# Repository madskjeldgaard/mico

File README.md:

# Mico - A tiny, cheap Raspberry Pi Pico midi controller

Mico is a small, cheap (~10 euros total) and super precise 14 bit midi controller based on the [Raspberry Pi Pico board](https://www.raspberrypi.com/products/raspberry-pi-pico/).

## Features
- 4 x detentless (smooth) encoders 
- Velocity: Slow movements result in microscopic changes (1/16000 of the max range approximately), fast movements in large changes.
- A variety of "clip modes" (cycle through them by pressing the button):
 	- wrap (when the value goes above max, it wraps back to 0) 
 	- clamp (clip at min and max value)
- 14 bit midi (as well as regular 7 bit midi)
- Cheap as chips and open sourced

## DEMO

There's a [demo here](https://vimeo.com/723291413).

## BOM

| Quantity | Part | Mouser Number |
|---|---|---|
| 1 | Raspberry Pi Pico rpi2040 | [474-DEV-17829](https://no.mouser.com/ProductDetail/SparkFun/DEV-17829?qs=sGAEpiMZZMv0NwlthflBi8NxDpSYKEiM3fbb2%2FVBX4k%3D) |
| 8 | 0.01uF capacitor, 0603 | [80-C0603C103M5R7411](https://no.mouser.com/ProductDetail/KEMET/C0603C103M5RAC7411?qs=ACslrEyEXNOtANB4TBkCnQ%3D%3D) |
| 16 | 10k resistors, 1%, 0603 | [603-RC0603FR-0710KL](https://no.mouser.com/ProductDetail/YAGEO/RC0603FR-0710KL?qs=sGAEpiMZZMtlubZbdhIBIAhzU1Tw%252BHVakiDuQ4Zki0U%3D) |
| 4 | 15mm Detentless encoders | [652-PEC11R-4015K-N24](https://no.mouser.com/ProductDetail/652-PEC11R-4015K-N24)(knurled) / [PEC11R-4015F-N0024](https://no.mouser.com/ProductDetail/Bourns/PEC11R-4015F-N0024)(flat) |
| 2 | Female header (to sandwich between the boards)| n/a |
| 2 | Male header (to sandwich between the boards) | n/a |

## Uploading the firmware

Download the latest firmware from the release and locate the `mico.uf2` file. While plugging your Pico into your computer, press and hold the "BOOTSEL" button. It will show up as a storage device on your computer. Copy `mico.uf2` to this device. Done.

## Building and uploading the firmware (optional)

If you want to build the code and mess around with it, it is recommended to use a second Pico flashed with the [picoprobe](https://github.com/raspberrypi/picoprobe) firmware.

### Using picoprobe

```bash
cd software
mkdir build
cd build 
cmake ..
make && openocd -f interface/picoprobe.cfg -f target/rp2040.cfg -c "program mico.elf verify reset exit"
```
Debug:
```bash
openocd -f interface/picoprobe.cfg -f target/rp2040.cfg -s tcl
```

## Usage

### SuperCollider

There is an easy to use interface for this controller [here](https://github.com/madskjeldgaard/mico-sc).

## License

This work is shared under the *Attribution-NonCommercial-ShareAlike 4.0 International* license.

If you have questions about that, send me an email **mail at madskjeldgaard.dk**

## Credits

These projects were a big help and inspiration in making this:
- [schatzmann blog](https://www.pschatzmann.ch/home/2021/02/15/usb-midi-on-the-arduino-pico/) and [also this post](https://www.pschatzmann.ch/home/2021/02/19/tinyusb-a-simple-tutorial/)
- [pico-example-midi](https://github.com/infovore/pico-example-midi)
- [encoder-pio](https://github.com/pimoroni/pimoroni-pico) is from the pimoroni-pico library. MIT Licensed.

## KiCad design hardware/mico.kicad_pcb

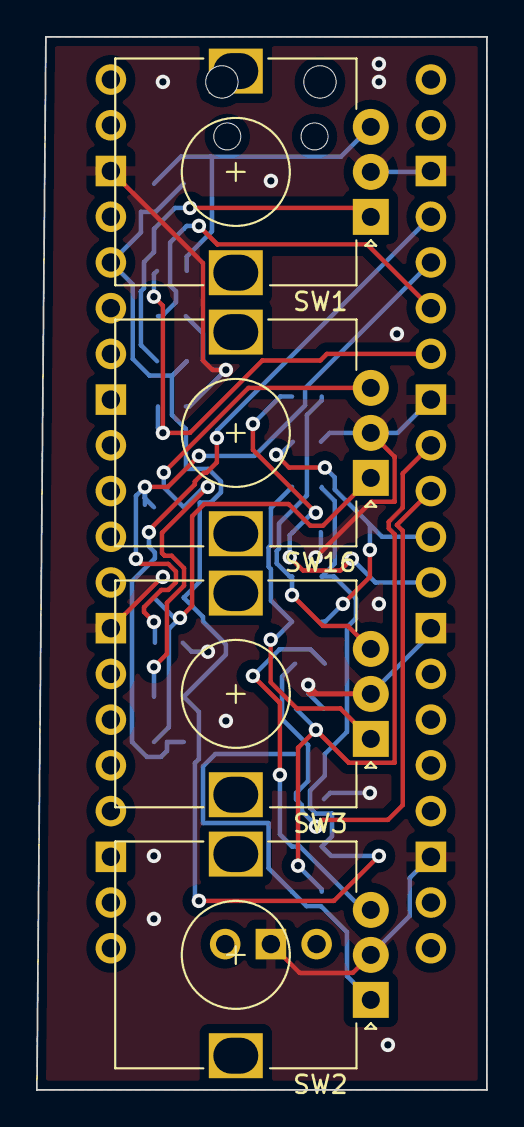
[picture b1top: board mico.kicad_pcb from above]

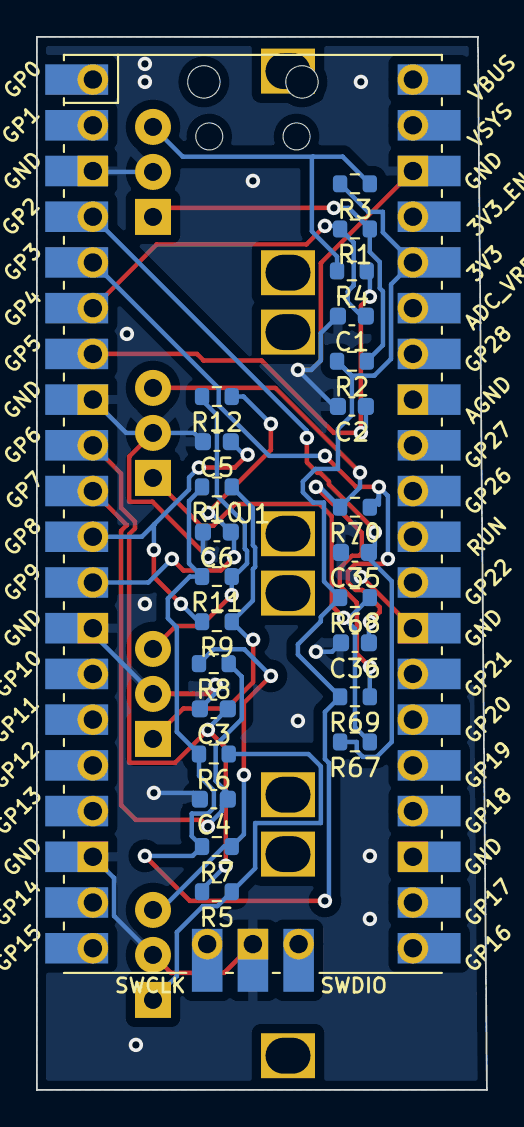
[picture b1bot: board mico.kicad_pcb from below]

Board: 2 copper layers, 25.0 x 58.5 mm, 29 parts (25 on the bottom side), 18 nets.

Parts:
C1, C2, C3, C4, C5, C6, C35, C36: 0.01uF; C_0603_1608Metric
R1, R2, R3, R4, R5, R6, R7, R8, R9, R10, R11, R12, R67, R68, R69, R70: 10k; R_0603_1608Metric
SW1, SW2, SW3, SW16: Rotary_Encoder; RotaryEncoder_Alps_EC12E_Vertical_H20mm
U1: Pico; RPi_Pico_SMD_TH

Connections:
+3V3: R2.2, R3.2, R6.2, R7.2, R10.2, R11.2, R68.2, R69.2, U1.36 (3V3)
/encoder_no_switch1/A: C1.1, R1.2, U1.6 (GPIO4)
/encoder_no_switch1/B: C2.1, R4.1, U1.7 (GPIO5)
/encoder_no_switch2/A: C3.1, R5.2, U1.9 (GPIO6)
/encoder_no_switch2/B: C4.1, R8.1, U1.10 (GPIO7)
/encoder_no_switch3/A: C5.1, R9.2, U1.11 (GPIO8)
/encoder_no_switch3/B: C6.1, R12.1, U1.12 (GPIO9)
/encoder_no_switch/A: C35.1, R67.2, U1.4 (GPIO2)
/encoder_no_switch/B: C36.1, R70.1, U1.5 (GPIO3)
GND: C1.2, C2.2, C3.2, C4.2, C5.2, C6.2, C35.2, C36.2, SW1.C, SW2.C, SW3.C, SW16.C, U1.3 (GND), U1.8 (GND), U1.13 (GND), U1.18 (GND), U1.28 (GND), U1.38 (GND), U1.42 (GND)
unnamed: R1.1, R2.1, SW1.A
unnamed: R3.1, R4.2, SW1.B
unnamed: R5.1, R6.1, SW2.A
unnamed: R7.1, R8.2, SW2.B
unnamed: R9.1, R10.1, SW3.A
unnamed: R11.1, R12.2, SW3.B
unnamed: R67.1, R68.1, SW16.A
unnamed: R69.1, R70.2, SW16.B

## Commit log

2022-01-27 gerbers
2022-02-23 non-working software
2022-02-23 harware v1 done
2022-02-23 non-working enclosure
2022-02-23 make it work with some of the hardware
2022-02-23 up ign
2022-02-23 license and info
2022-02-23 nice
2022-02-23 todo
2022-02-24 rename Encoder to PioEncoder and make MicoEncoder class
2022-02-24 readme
2022-02-24 table
2022-02-25 micoencoder progress
2022-02-25 more of the good stuff
2022-02-25 add initial usb midi support
2022-02-25 ignore
2022-02-25 finish basic midi support
2022-02-26 basic 8 bit midi cc support added
2022-02-26 Move midi and utility stuff t seperate header
2022-02-26 Midi stuff done
2022-02-26 build info
2022-02-27 fix bug in 14 bit midi sender
2022-02-27 Mico-encoder class finished and all encoders now working
2022-02-27 house cleaning
2022-02-27 up readme
2022-02-27 feat: cycle through clip modes using button
2022-02-28 Refactor each encoder as a MicoVoice
2022-03-01 Move all tasks into timer
2022-03-01 docs update
2022-03-01 fix: time_delta could potentially add max value infinitely if 0
2022-03-01 cleanup
2022-03-01 Tune velocity a bit
2022-03-02 add 3d models to pcb layout
2022-03-02 Make 3d model of all electronics (for enclosure work)
2022-03-02 add enclosure
2022-03-02 add license
2022-03-02 images
2022-03-02 info
2022-03-02 new headline
2022-03-02 headers
2022-03-03 finish print
2022-03-03 tune box
2022-03-25 feat: Add initial derivative support
2022-03-26 Initial support for velocity trigger note on/off
2022-06-22 fix: Change midi cc channels to go from 14
2022-06-22 fix: make parallel mode optional using flag
2022-06-22 fix: Clamping mode did not clamp to 0.0-1.0
2022-06-22 docs: add picture
2022-06-22 fix!: change license
2022-06-22 license
2022-06-22 docs: sc link
2022-06-23 add demo
2022-09-03 fix: Midi timer not called often enough for MacOS
2023-07-13 dont set sdk path by default
